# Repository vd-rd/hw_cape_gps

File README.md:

## Overview
Designed for accurate positioning inside embedded projects, this GPS cape offers extended telemetry information, as well as multiple choices for antenna type and placing as well as SoC options.
 The module is designed to accept either:
  - Fibocom GTS-4E-60 (tested)
  - Simcom SIM-28
  - uBlox Neo-M6/7/8
 Regarding connectivity options, the module can be equipped with either an active or passive antenna, connected via a standard u.Fl connector or placed on the carrier PCB.
Detailed information about positioning capabilities of the module can be found in the [GPS](/doc/gps.md) page.

### Project notes
Current development is on the master branch. Earlier revisions have been moved on the archive branch.

### Resources
You can find all necesary information to build or evaluate the module here:
   - [View 3D board render](https://a360.co/2DnqBSM)
   - [Fabrication files](https://github.com/vd-rd/hw_cape_gps/releases)
 
## Features
 - Low power consumption (<30mA)
 - Board can be placed in a true shutdown state (<20uA)
 - Extended temperature range of operation (-40C - 85)
 Detailed information about technical capabilities of the module can be found in the [hardware description](/docs/hardware.md) page.

## Telemetry data
 The module is able to provide standard NMEA sentences on a UART interface. Supported sentences:
 - $GPGGA - Time, position and fix type data
 - $GPGSA - GPS receiver operating mode, satellites used in the position solution, and DOP values
 - $GPGSV - Number of GPS satellites in view satellite ID numbers, elevation, azimuth, & SNR values
 - $GPRMC - Time, date, position, course and speed data
Detailed information about the sentences and parameters can be found in [telemetry](/docs/telemetry.md) page.

## Production
 The module is designed on a 40x40mm double layer PCB, with components placed on a single side for easy assembly.
 The total height of the module (without connectors mounted) is 3mm without the passive antenna mounted and 10mm otherwise.
 Detailed information about the stack-up, BOM and configuration options can be found on the [manufacturing](/docs/manufacturing.md) page.

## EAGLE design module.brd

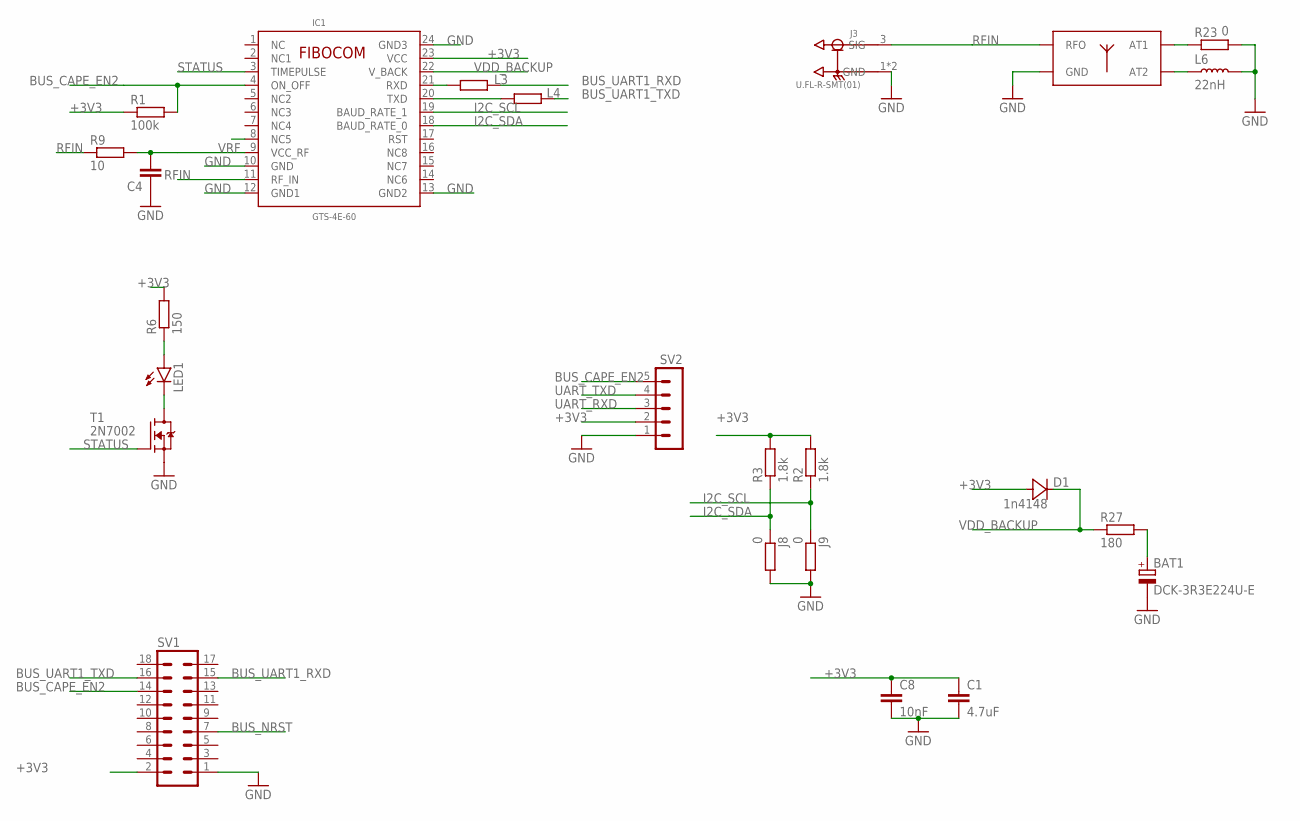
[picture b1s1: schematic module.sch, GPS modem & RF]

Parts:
ANT1: M20047; PCBCOMPONENT_1
BAT1: DCK-3R3E224U-E; 621
C1: 4.7uF; C0603
C4: 10nF; C0402K
C8: 10nF; C0603
D1: 1n4148; SOD323
IC1: GTS-4E-60; _GTS_4E_60
J3: U.FL-R-SMT(01); HRS_U.FL-R-SMT(01)
J8, J9: 0; R0603
L3, L4: blm15; R0603
L6: 22nH; L0402
LED1: LEDCHIP-LED0603; CHIP-LED0603
R1: 100k; R0603
R2, R3: 1.8k; R0603
R6: 150; R0603
R9: 10; R0402
R23: 0; R0402
R27: 180; R0603
SV1: MA09-2
SV2: MA05-1
T1: 2N7002; SOT95P240X110-3

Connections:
+3V3: C1.1, C8.1, D1.A, IC1.23 (VCC), R1.1, R2.2, R3.2, R6.2, SV1.2, SV2.2
BUS_CAPE_EN2: IC1.4 (ON_OFF), R1.2, SV1.14, SV2.5
BUS_NRST: SV1.7
BUS_UART1_RXD: L3.2, SV1.15
BUS_UART1_TXD: L4.2, SV1.16
GND: ANT1.2 (GND), ANT1.3 (GND), ANT1.4 (GND), BAT1.-, C1.2, C4.1, C8.2, IC1.10 (GND), IC1.12 (GND1), IC1.13 (GND2), IC1.24 (GND3), J3.1 (GND), J3.2 (GND), J8.2, J9.2, L6.2, R23.2, SV1.1, SV2.1, T1.2 (S)
I2C_SCL: IC1.19 (BAUD_RATE_1), J9.1, R2.1
I2C_SDA: IC1.18 (BAUD_RATE_0), J8.1, R3.1
unnamed: LED1.C, T1.3 (D)
unnamed: LED1.A, R6.1
unnamed: ANT1.1 (AT1), R23.1
unnamed: ANT1.6 (AT2), L6.1
unnamed: BAT1.+, R27.2
RFIN: ANT1.5 (RFO), IC1.11 (RF_IN), J3.3 (SIG), R9.1
STATUS: IC1.3 (TIMEPULSE), T1.1 (G)
UART_RXD: IC1.20 (TXD), L4.1, SV2.3
UART_TXD: IC1.21 (RXD), L3.1, SV2.4
VDD_BACKUP: D1.K (C), IC1.22 (V_BACK), R27.1
VRF: C4.2, IC1.9 (VCC_RF), R9.2

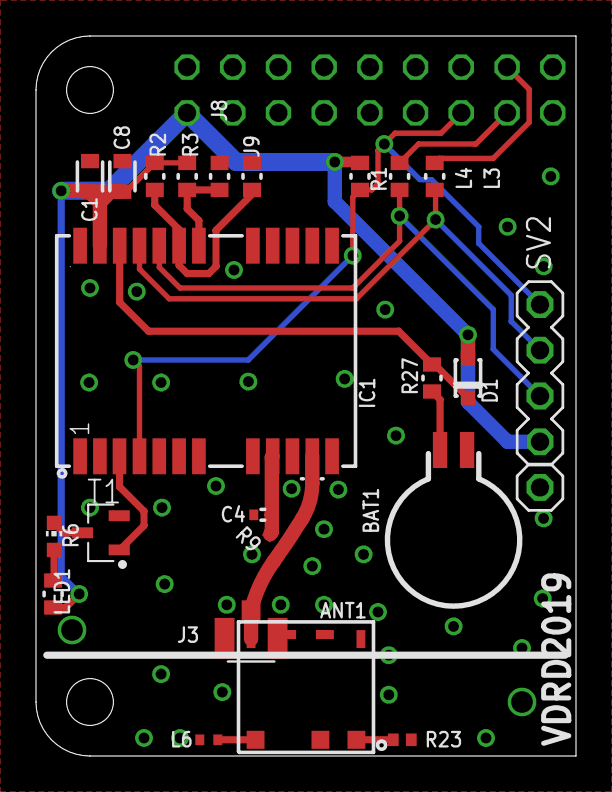
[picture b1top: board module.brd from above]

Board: 2 copper layers, 30.0 x 40.0 mm, 24 parts (1 on the bottom side), 18 nets.

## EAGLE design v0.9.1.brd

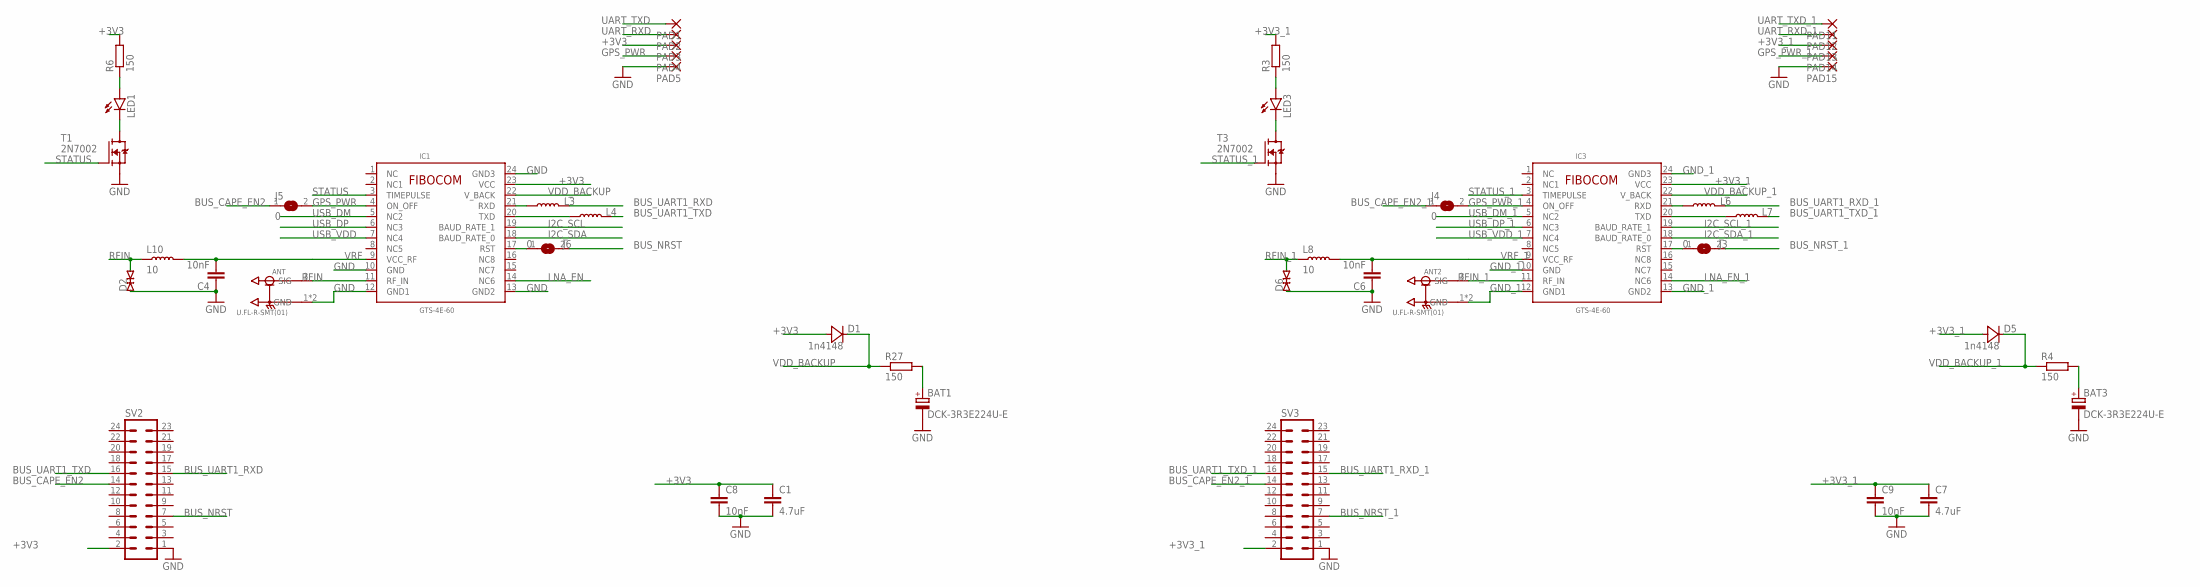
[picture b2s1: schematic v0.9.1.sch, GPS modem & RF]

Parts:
ANT, ANT2: U.FL-R-SMT(01); HRS_U.FL-R-SMT(01)
BAT1, BAT3: DCK-3R3E224U-E; 621
C1, C7: 4.7uF; C0603
C4, C6: 10nF; C0402K
C8, C9: 10nF; C0603
D1, D5: 1n4148; SOD323
D2, D6: ESD9B5.0ST5G; SOD1006X40
IC1, IC3: GTS-4E-60; _GTS_4E_60
J3, J4, J5, J6: 0; C0603
L3, L4, L6, L7: blm15; L0402
L8, L10: 10; L0402
LED1, LED3: LEDCHIP-LED0603; CHIP-LED0603
PAD1, PAD2, PAD3, PAD4, PAD5, PAD11, PAD12, PAD13, PAD14, PAD15: 1,6/0,9
R3, R4, R6, R27: 150; R0603
SV2, SV3: MA12-2
T1, T3: 2N7002; SOT95P240X110-3

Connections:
+3V3: C1.1, C8.1, D1.A, IC1.23 (VCC), PAD3.1, R6.2, SV2.2
+3V3_1: C7.1, C9.1, D5.A, IC3.23 (VCC), PAD13.1, R3.2, SV3.2
BUS_CAPE_EN2: J5.1, SV2.14
BUS_CAPE_EN2_1: J4.1, SV3.14
BUS_NRST: J6.2, SV2.7
BUS_NRST_1: J3.2, SV3.7
BUS_UART1_RXD: L3.2, SV2.15
BUS_UART1_RXD_1: L6.2, SV3.15
BUS_UART1_TXD: L4.2, SV2.16
BUS_UART1_TXD_1: L7.2, SV3.16
GND: ANT.1 (GND), ANT.2 (GND), BAT1.-, C1.2, C4.1, C8.2, D2.1 (A), IC1.10 (GND), IC1.12 (GND1), IC1.13 (GND2), IC1.24 (GND3), PAD5.1, SV2.1, T1.2 (S)
GND_1: ANT2.1 (GND), ANT2.2 (GND), BAT3.-, C6.1, C7.2, C9.2, D6.1 (A), IC3.10 (GND), IC3.12 (GND1), IC3.13 (GND2), IC3.24 (GND3), PAD15.1, SV3.1, T3.2 (S)
GPS_PWR: IC1.4 (ON_OFF), J5.2, PAD4.1
GPS_PWR_1: IC3.4 (ON_OFF), J4.2, PAD14.1
I2C_SCL: IC1.19 (BAUD_RATE_1)
I2C_SCL_1: IC3.19 (BAUD_RATE_1)
I2C_SDA: IC1.18 (BAUD_RATE_0)
I2C_SDA_1: IC3.18 (BAUD_RATE_0)
LNA_EN: IC1.14 (NC6)
LNA_EN_1: IC3.14 (NC6)
unnamed: BAT3.+, R4.2
unnamed: LED1.C, T1.3 (D)
unnamed: IC3.17 (RST), J3.1
unnamed: IC1.17 (RST), J6.1
unnamed: LED3.C, T3.3 (D)
unnamed: LED3.A, R3.1
unnamed: LED1.A, R6.1
unnamed: BAT1.+, R27.2
RFIN: ANT.3 (SIG), D2.2 (C), IC1.11 (RF_IN), L10.1
RFIN_1: ANT2.3 (SIG), D6.2 (C), IC3.11 (RF_IN), L8.1
STATUS: IC1.3 (TIMEPULSE), T1.1 (G)
STATUS_1: IC3.3 (TIMEPULSE), T3.1 (G)
UART_RXD: IC1.20 (TXD), L4.1, PAD2.1
UART_RXD_1: IC3.20 (TXD), L7.1, PAD12.1
UART_TXD: IC1.21 (RXD), L3.1, PAD1.1
UART_TXD_1: IC3.21 (RXD), L6.1, PAD11.1
USB_DM: IC1.5 (NC2)
USB_DM_1: IC3.5 (NC2)
USB_DP: IC1.6 (NC3)
USB_DP_1: IC3.6 (NC3)
USB_VDD: IC1.7 (NC4)
USB_VDD_1: IC3.7 (NC4)
VDD_BACKUP: D1.K (C), IC1.22 (V_BACK), R27.1
VDD_BACKUP_1: D5.K (C), IC3.22 (V_BACK), R4.1
VRF: C4.2, IC1.9 (VCC_RF), L10.2
VRF_1: C6.2, IC3.9 (VCC_RF), L8.2

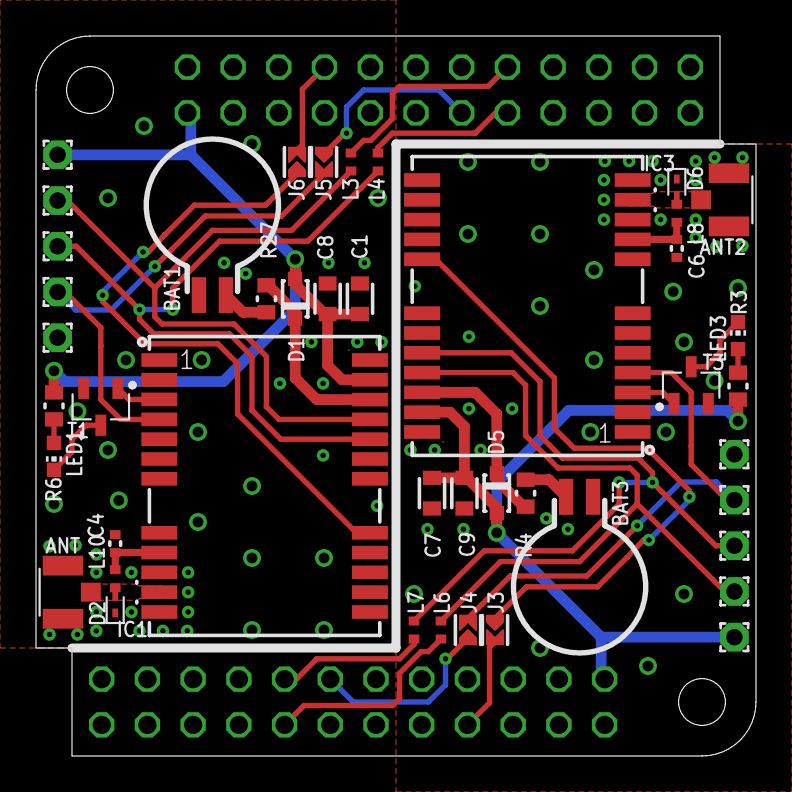
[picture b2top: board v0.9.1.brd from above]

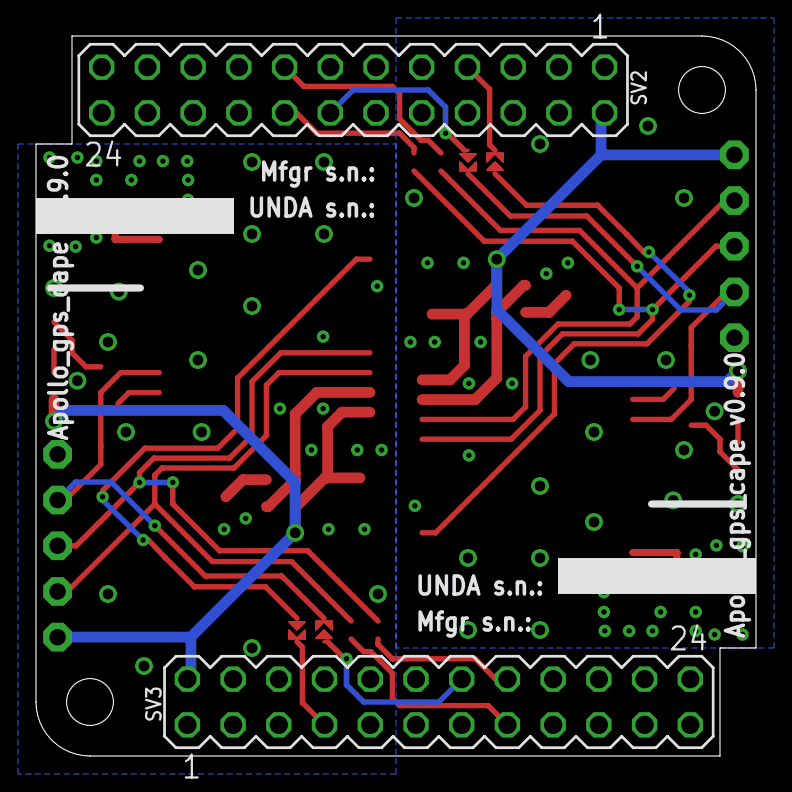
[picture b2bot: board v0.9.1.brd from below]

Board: 2 copper layers, 40.0 x 40.0 mm, 46 parts (2 on the bottom side), 34 nets.

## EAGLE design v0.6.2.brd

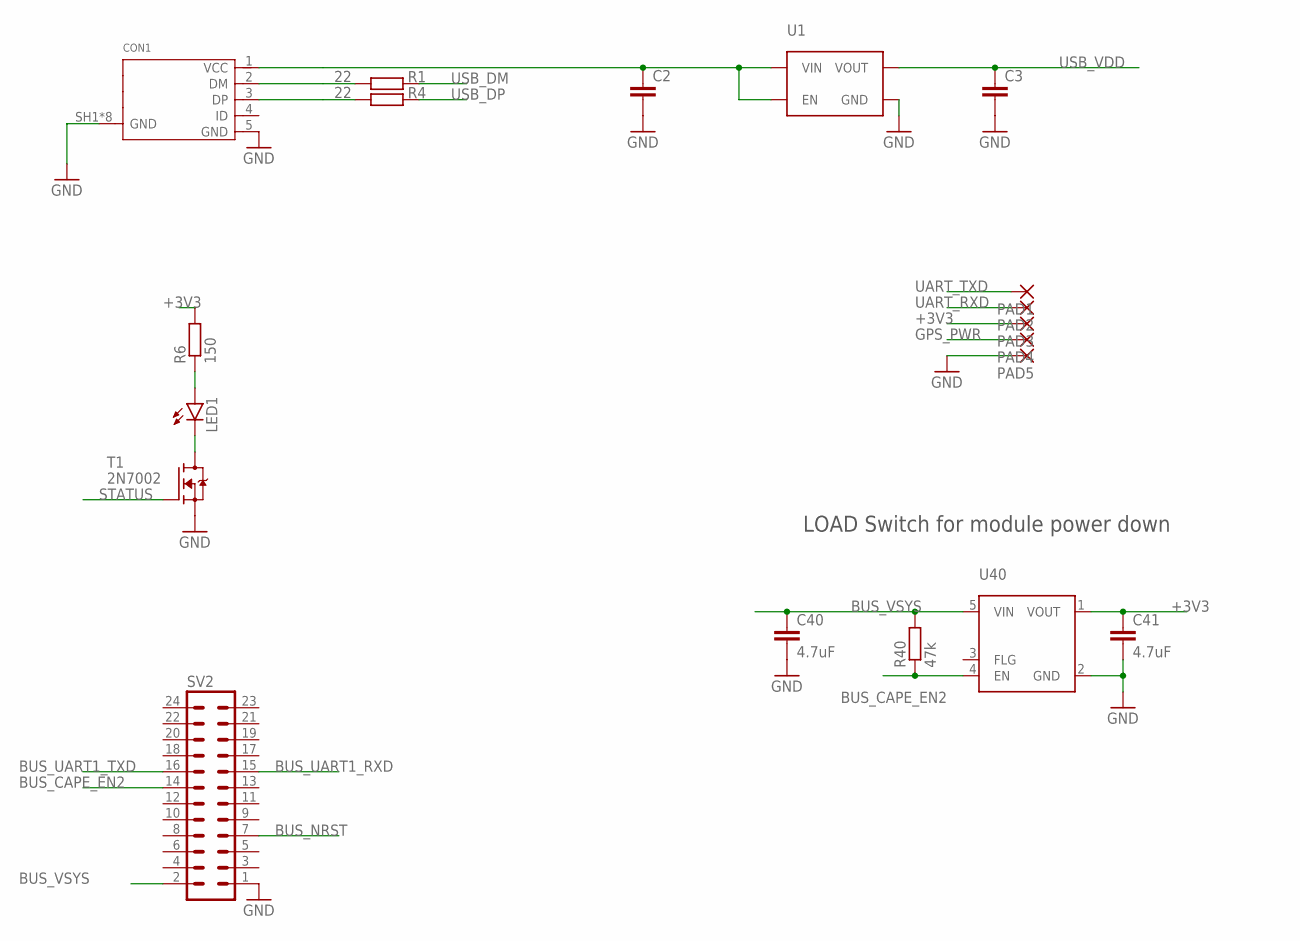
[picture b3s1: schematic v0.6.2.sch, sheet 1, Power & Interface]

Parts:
C2, C3: C-EUC0603; C0603
C40, C41: 4.7uF; C0603
CON1: 10118194-0001LF; 10118194
LED1: LEDCHIP-LED0603; CHIP-LED0603
PAD1, PAD2, PAD3, PAD4, PAD5: 1,6/0,9
R1, R4: 22; R0402
R6: 150; R0402
R40: 47k; R0402
SV2: MA12-2
T1: 2N7002; SOT95P240X110-3
U1: MIC94310; SOT95P280X110-5
U40: AP22802b; SOT25

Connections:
+3V3: C41.1, PAD3.1, R6.2, U40.1 (VOUT); also elsewhere on the board
BUS_CAPE_EN2: R40.1, SV2.14, U40.4 (EN); also elsewhere on the board
BUS_NRST: SV2.7; also elsewhere on the board
BUS_UART1_RXD: SV2.15; also elsewhere on the board
BUS_UART1_TXD: SV2.16; also elsewhere on the board
BUS_VSYS: C40.1, R40.2, SV2.2, U40.5 (VIN)
GND: C2.2, C3.2, C40.2, C41.2, CON1.5 (GND), CON1.SH1 (GND), CON1.SH2 (GND), CON1.SH3 (GND), CON1.SH4 (GND), CON1.SH5 (GND), CON1.SH6 (GND), CON1.SH7 (GND), CON1.SH8 (GND), PAD5.1, SV2.1, T1.2 (S), U1.2 (GND), U40.2 (GND); also elsewhere on the board
GPS_PWR: PAD4.1; also elsewhere on the board
unnamed: LED1.C, T1.3 (D)
unnamed: CON1.2 (DM), R1.2
unnamed: CON1.3 (DP), R4.2
unnamed: LED1.A, R6.1
unnamed: C2.1, CON1.1 (VCC), U1.1 (VIN), U1.3 (EN)
STATUS: T1.1 (G); also elsewhere on the board
UART_RXD: PAD2.1; also elsewhere on the board
UART_TXD: PAD1.1; also elsewhere on the board
USB_DM: R1.1; also elsewhere on the board
USB_DP: R4.1; also elsewhere on the board
USB_VDD: C3.1, U1.5 (VOUT); also elsewhere on the board

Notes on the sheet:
LOAD Switch for module power down

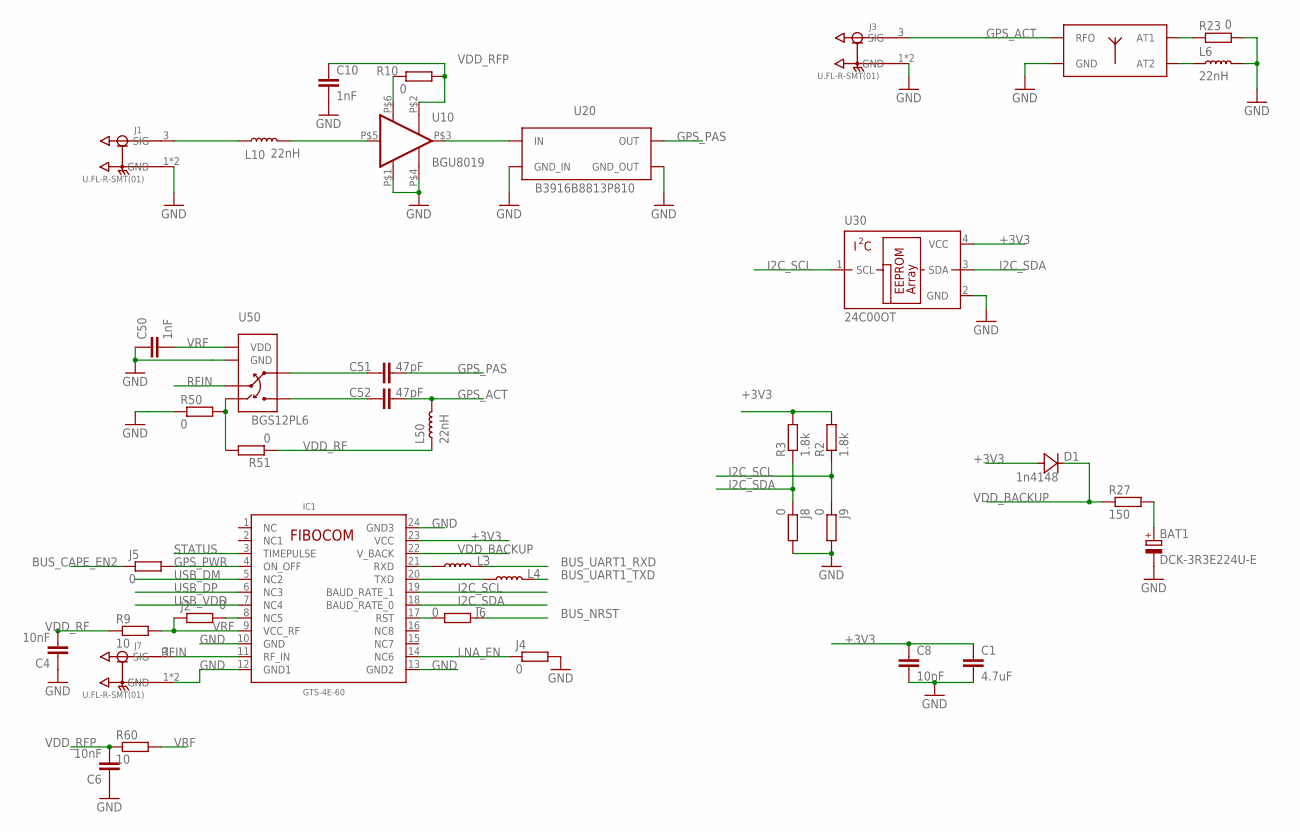
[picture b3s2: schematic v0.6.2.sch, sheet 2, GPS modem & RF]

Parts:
ANT1: M20047; PCBCOMPONENT_1
BAT1: DCK-3R3E224U-E; 621
C1: 4.7uF; C0603
C4, C6, C8: 10nF; C0402K
C10, C50: 1nF; C0402K
C51, C52: 47pF; C0402K
D1: 1n4148; SOD323
IC1: GTS-4E-60; _GTS_4E_60
J1, J3, J7: U.FL-R-SMT(01); HRS_U.FL-R-SMT(01)
J2, J4, J5, J6, J8, J9: 0; R0402
L3, L4: blm15; L0402
L6, L10, L50: 22nH; L0402
R2, R3: 1.8k; R0402
R9, R60: 10; R0402
R10, R23, R50, R51: 0; R0402
R27: 150; R0402
U10: BGU8019; XSON6
U20: B3916B8813P810; XSON5
U30: 24C00OT; SOT23-5L
U50: BGS12PL6; TSLP-6-4

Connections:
+3V3: C1.1, C8.1, D1.A, IC1.23 (VCC), R2.2, R3.2, U30.4 (VCC); also elsewhere on the board
BUS_CAPE_EN2: J5.1; also elsewhere on the board
BUS_NRST: J6.2; also elsewhere on the board
BUS_UART1_RXD: L3.2; also elsewhere on the board
BUS_UART1_TXD: L4.2; also elsewhere on the board
GND: ANT1.2 (GND), ANT1.3 (GND), ANT1.4 (GND), BAT1.-, C1.2, C4.1, C6.1, C8.2, C10.2, C50.1, IC1.10 (GND), IC1.12 (GND1), IC1.13 (GND2), IC1.24 (GND3), J1.1 (GND), J1.2 (GND), J3.1 (GND), J3.2 (GND), J4.2, J7.1 (GND), J7.2 (GND), J8.2, J9.2, L6.2, R23.2, R50.1, U10.P$1 (GND), U10.P$4 (GND_RF), U20.2 (GND_IN), U20.3 (GND_OUT), U20.5 (GND_IN), U30.2 (GND), U50.P$2 (GND); also elsewhere on the board
GPS_ACT: ANT1.5 (RFO), C52.2, J3.3 (SIG), L50.2
GPS_PAS: C51.2, U20.4 (OUT)
GPS_PWR: IC1.4 (ON_OFF), J5.2; also elsewhere on the board
I2C_SCL: IC1.19 (BAUD_RATE_1), J9.1, R2.1, U30.1 (SCL)
I2C_SDA: IC1.18 (BAUD_RATE_0), J8.1, R3.1, U30.3 (SDA)
LNA_EN: IC1.14 (NC6), J4.1
unnamed: IC1.8 (NC5), J2.2
unnamed: U10.P$3 (RF_OUT), U20.1 (IN)
unnamed: R10.1, U10.P$6 (ENABLE)
unnamed: L10.2, U10.P$5 (RF_IN)
unnamed: J1.3 (SIG), L10.1
unnamed: IC1.17 (RST), J6.1
unnamed: R50.2, R51.2, U50.P$6
unnamed: C51.1, U50.P$3 (RF1)
unnamed: C52.1, U50.P$1 (RF2)
unnamed: ANT1.1 (AT1), R23.1
unnamed: ANT1.6 (AT2), L6.1
unnamed: BAT1.+, R27.2
RFIN: IC1.11 (RF_IN), J7.3 (SIG), U50.P$5 (RFIN)
STATUS: IC1.3 (TIMEPULSE); also elsewhere on the board
UART_RXD: IC1.20 (TXD), L4.1; also elsewhere on the board
UART_TXD: IC1.21 (RXD), L3.1; also elsewhere on the board
USB_DM: IC1.5 (NC2); also elsewhere on the board
USB_DP: IC1.6 (NC3); also elsewhere on the board
USB_VDD: IC1.7 (NC4); also elsewhere on the board
VDD_BACKUP: D1.K (C), IC1.22 (V_BACK), R27.1
VDD_RF: C4.2, L50.1, R9.1, R51.1
VDD_RFP: C6.2, C10.1, R10.2, R60.1, U10.P$2 (VCC)
VRF: C50.2, IC1.9 (VCC_RF), J2.1, R9.2, R60.2, U50.P$4 (VDD)

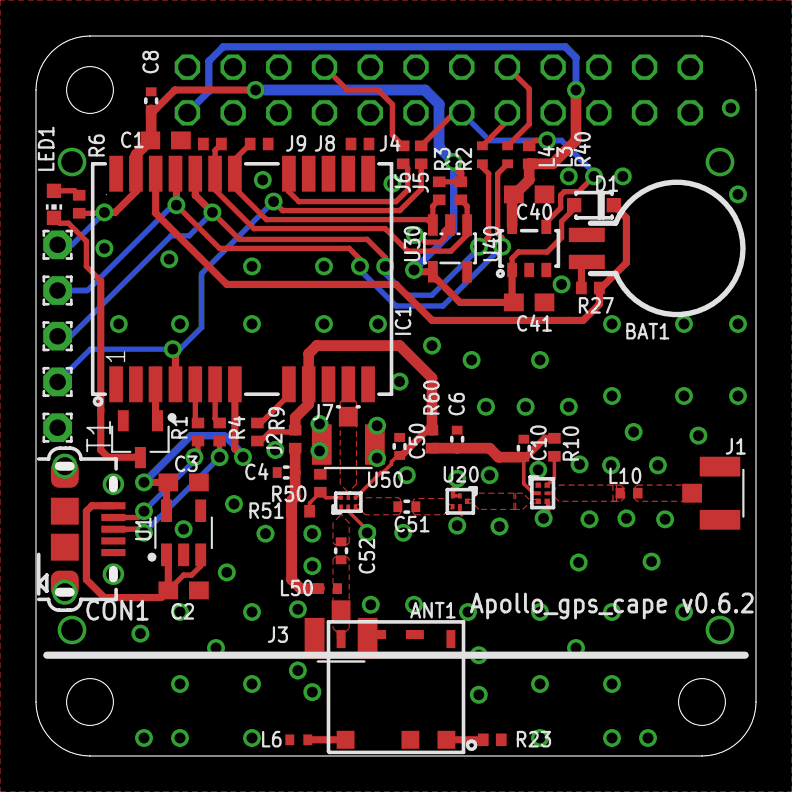
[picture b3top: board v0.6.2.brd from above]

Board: 2 copper layers, 40.0 x 40.0 mm, 58 parts (1 on the bottom side), 41 nets.

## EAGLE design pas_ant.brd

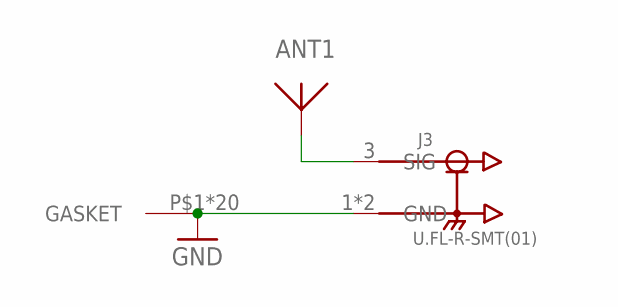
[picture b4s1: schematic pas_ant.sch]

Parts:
ANT1: ANT1590-2540A; 2540A
J3: U.FL-R-SMT(01); HRS_U.FL-R-SMT(01)
U$1: 2118718-2; 2118717-2

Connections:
GND2: J3.1 (GND), J3.2 (GND), U$1.P$1, U$1.P$2, U$1.P$3, U$1.P$4, U$1.P$5, U$1.P$6, U$1.P$7, U$1.P$8, U$1.P$9, U$1.P$10, U$1.P$11, U$1.P$12, U$1.P$13, U$1.P$14, U$1.P$15, U$1.P$16, U$1.P$17, U$1.P$18, U$1.P$19, U$1.P$20
unnamed: ANT1.P$1, J3.3 (SIG)

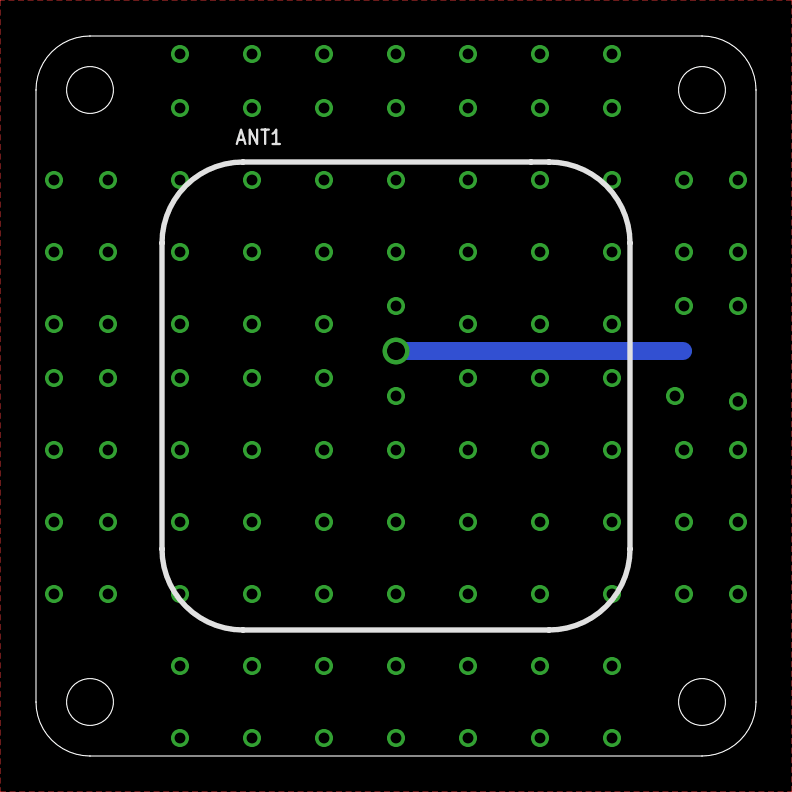
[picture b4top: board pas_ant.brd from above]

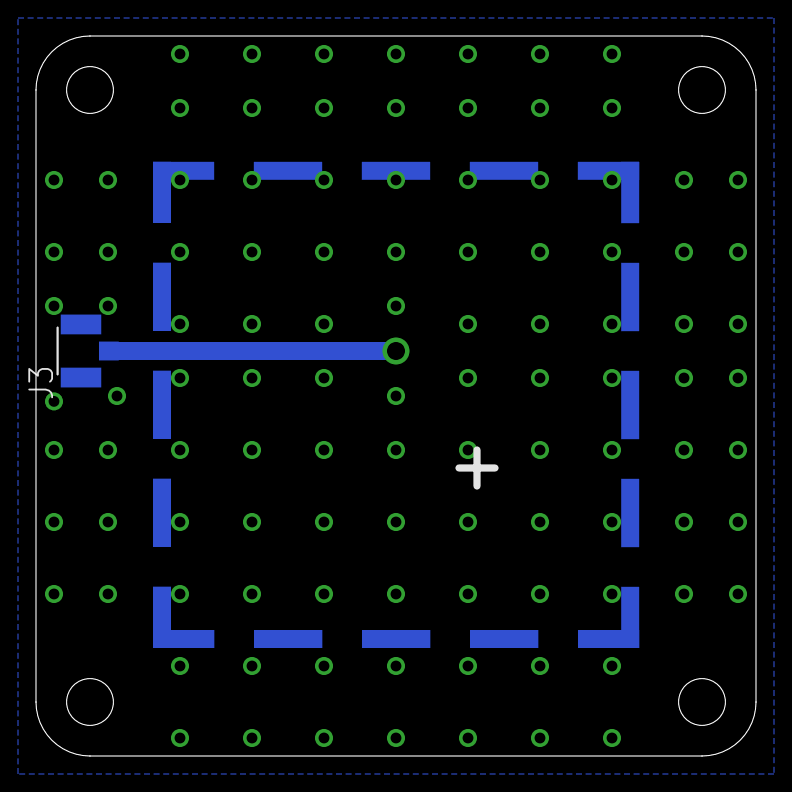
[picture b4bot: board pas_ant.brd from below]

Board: 2 copper layers, 40.0 x 40.0 mm, 3 parts (2 on the bottom side), 2 nets.

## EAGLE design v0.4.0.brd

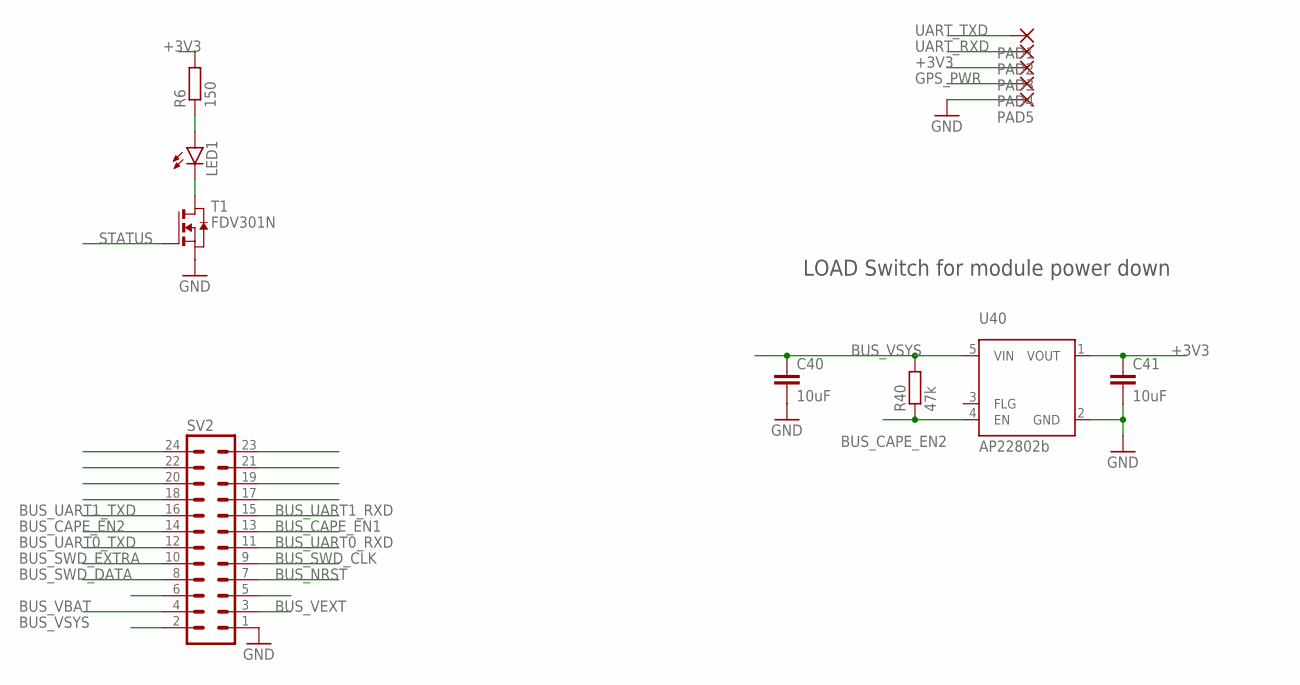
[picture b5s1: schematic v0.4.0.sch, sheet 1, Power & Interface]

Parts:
C40, C41: 10uF; C0603
LED1: LEDCHIP-LED0603; CHIP-LED0603
PAD1, PAD2, PAD3, PAD4, PAD5: 1,6/0,9
R6: 150; R0402
R40: 47k; R0402
SV2: MA12-2
T1: FDV301N; SOT-23
U40: AP22802b; SOT25

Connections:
+3V3: C41.1, PAD3.1, R6.2, U40.1 (VOUT); also elsewhere on the board
BUS_CAPE_EN1: SV2.13
BUS_CAPE_EN2: R40.1, SV2.14, U40.4 (EN); also elsewhere on the board
BUS_NRST: SV2.7; also elsewhere on the board
BUS_SWD_CLK: SV2.9
BUS_SWD_DATA: SV2.8
BUS_SWD_EXTRA: SV2.10
BUS_UART0_RXD: SV2.11
BUS_UART0_TXD: SV2.12
BUS_UART1_RXD: SV2.15; also elsewhere on the board
BUS_UART1_TXD: SV2.16; also elsewhere on the board
BUS_VBAT: SV2.4
BUS_VEXT: SV2.3
BUS_VSYS: C40.1, R40.2, SV2.2, U40.5 (VIN)
GND: C40.2, C41.2, PAD5.1, SV2.1, T1.2 (S), U40.2 (GND); also elsewhere on the board
GPS_PWR: PAD4.1; also elsewhere on the board
unnamed: LED1.C, T1.1 (D)
unnamed: LED1.A, R6.1
STATUS: T1.3 (G); also elsewhere on the board
UART_RXD: PAD2.1; also elsewhere on the board
UART_TXD: PAD1.1; also elsewhere on the board

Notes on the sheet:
LOAD Switch for module power down

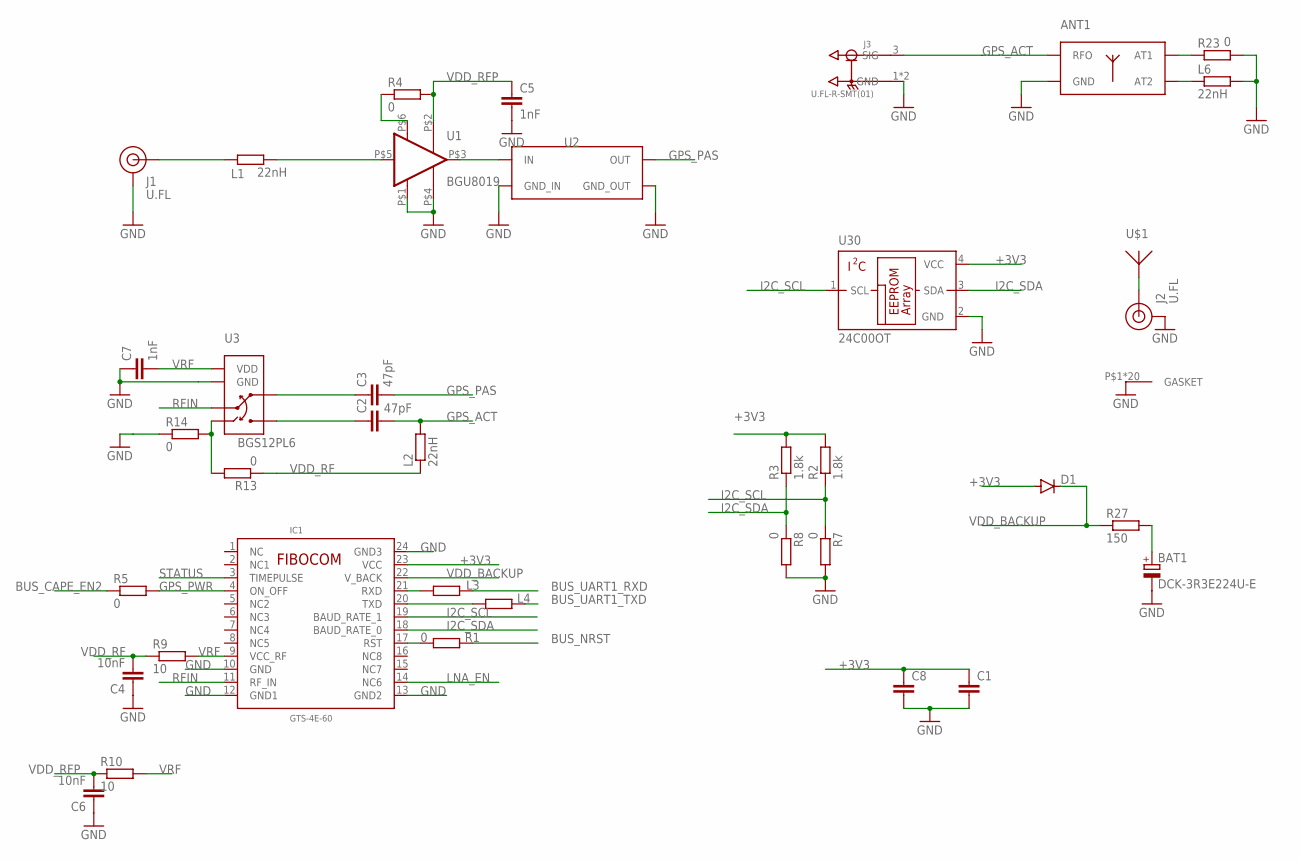
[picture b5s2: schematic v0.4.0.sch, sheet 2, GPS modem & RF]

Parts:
ANT1: M20047; PCBCOMPONENT_1
BAT1: DCK-3R3E224U-E; 621
C1: C-EUC0603; C0603
C2, C3: 47pF; C0402
C4, C6: 10nF; C0402
C5, C7: 1nF; C0402
C8: C-EUC0402; C0402
D1: DIODE-SOD323-R; SOD323-R
IC1: GTS-4E-60; _GTS_4E_60
J1, J2: U.FL
J3: U.FL-R-SMT(01); HRS_U.FL-R-SMT(01)
L1, L2, L6: 22nH; R0402
L3, L4: R-EU_R0402; R0402
R1, R4, R5, R7, R8, R13, R14, R23: 0; R0402
R2, R3: 1.8k; R0402
R9, R10: 10; R0402
R27: 150; R0402
U1: BGU8019; XSON6
U2: B3916B8813P810; XSON5
U3: BGS12PL6; TSLP-6-4
U30: 24C00OT; SOT23-5L
U$1: ANT1590-2540A; 2540A
U$2: 2118718-2; 2118717-2

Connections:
+3V3: C1.1, C8.1, D1.A, IC1.23 (VCC), R2.2, R3.2, U30.4 (VCC); also elsewhere on the board
BUS_CAPE_EN2: R5.1; also elsewhere on the board
BUS_NRST: R1.2; also elsewhere on the board
BUS_UART1_RXD: L3.2; also elsewhere on the board
BUS_UART1_TXD: L4.2; also elsewhere on the board
GND: ANT1.2 (GND), ANT1.3 (GND), ANT1.4 (GND), BAT1.-, C1.2, C4.1, C5.2, C6.1, C7.1, C8.2, IC1.10 (GND), IC1.12 (GND1), IC1.13 (GND2), IC1.24 (GND3), J1.1 (GND), J1.2 (GND), J2.1 (GND), J2.2 (GND), J3.1 (GND), J3.2 (GND), L6.2, R7.2, R8.2, R14.1, R23.2, U1.P$1 (GND), U1.P$4 (GND_RF), U2.2 (GND_IN), U2.3 (GND_OUT), U2.5 (GND_IN), U3.P$2 (GND), U30.2 (GND), U$2.P$1, U$2.P$2, U$2.P$3, U$2.P$4, U$2.P$5, U$2.P$6, U$2.P$7, U$2.P$8, U$2.P$9, U$2.P$10, U$2.P$11, U$2.P$12, U$2.P$13, U$2.P$14, U$2.P$15, U$2.P$16, U$2.P$17, U$2.P$18, U$2.P$19, U$2.P$20; also elsewhere on the board
GPS_ACT: ANT1.5 (RFO), C2.2, J3.3 (SIG), L2.2
GPS_PAS: C3.2, U2.4 (OUT)
GPS_PWR: IC1.4 (ON_OFF), R5.2; also elsewhere on the board
I2C_SCL: IC1.19 (BAUD_RATE_1), R2.1, R7.1, U30.1 (SCL)
I2C_SDA: IC1.18 (BAUD_RATE_0), R3.1, R8.1, U30.3 (SDA)
LNA_EN: IC1.14 (NC6)
unnamed: J2.FEED (SIGNAL), U$1.P$1
unnamed: U1.P$3 (RF_OUT), U2.1 (IN)
unnamed: R4.1, U1.P$6 (ENABLE)
unnamed: L1.2, U1.P$5 (RF_IN)
unnamed: J1.FEED (SIGNAL), L1.1
unnamed: IC1.17 (RST), R1.1
unnamed: R13.2, R14.2, U3.P$6
unnamed: C3.1, U3.P$3 (RF1)
unnamed: C2.1, U3.P$1 (RF2)
unnamed: ANT1.1 (AT1), R23.1
unnamed: ANT1.6 (AT2), L6.1
unnamed: BAT1.+, R27.2
RFIN: IC1.11 (RF_IN), U3.P$5 (RFIN)
STATUS: IC1.3 (TIMEPULSE); also elsewhere on the board
UART_RXD: IC1.20 (TXD), L4.1; also elsewhere on the board
UART_TXD: IC1.21 (RXD), L3.1; also elsewhere on the board
VDD_BACKUP: D1.C, IC1.22 (V_BACK), R27.1
VDD_RF: C4.2, L2.1, R9.1, R13.1
VDD_RFP: C5.1, C6.2, R4.2, R10.1, U1.P$2 (VCC)
VRF: C7.2, IC1.9 (VCC_RF), R9.2, R10.2, U3.P$4 (VDD)

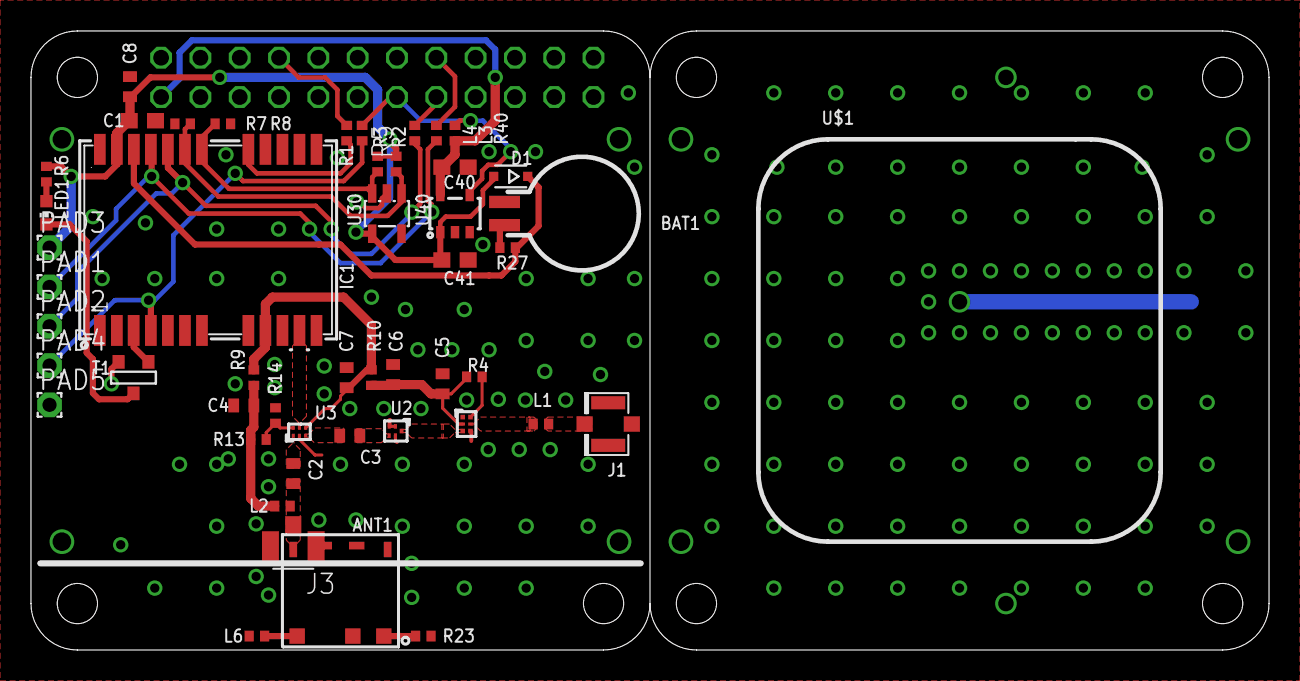
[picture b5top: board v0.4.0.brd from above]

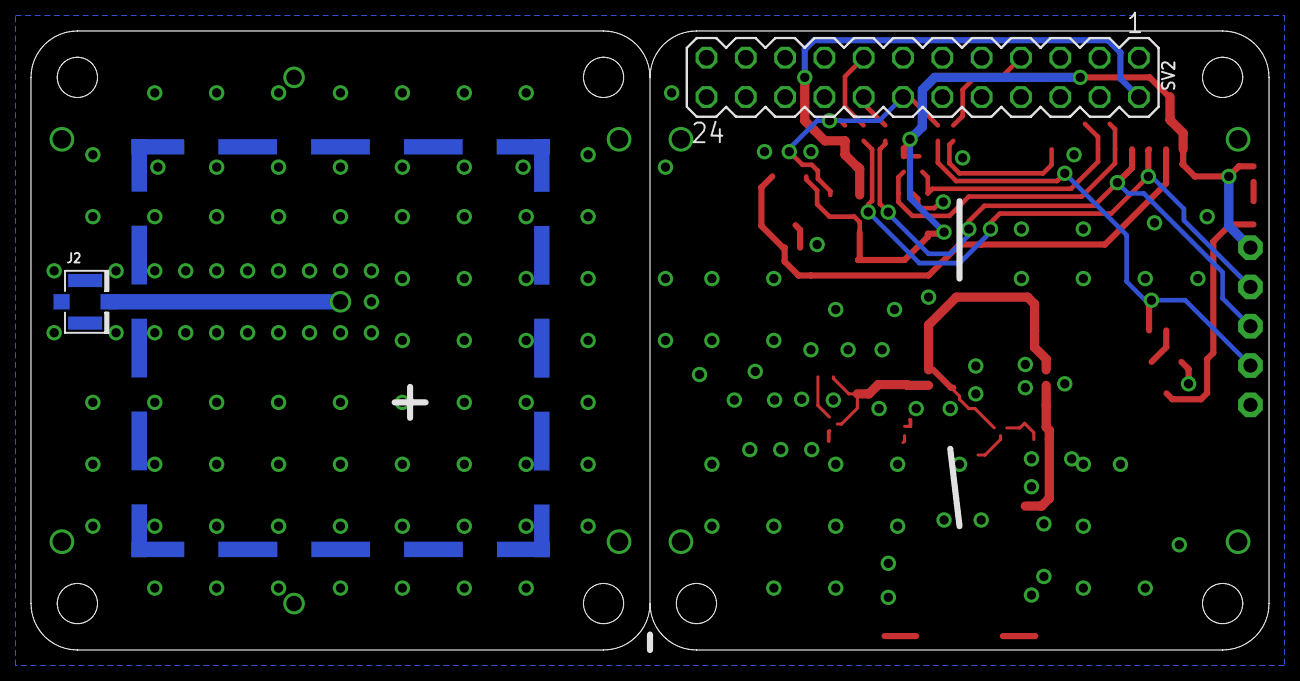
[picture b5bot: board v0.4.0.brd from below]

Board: 2 copper layers, 80.0 x 40.0 mm, 52 parts (3 on the bottom side), 34 nets.

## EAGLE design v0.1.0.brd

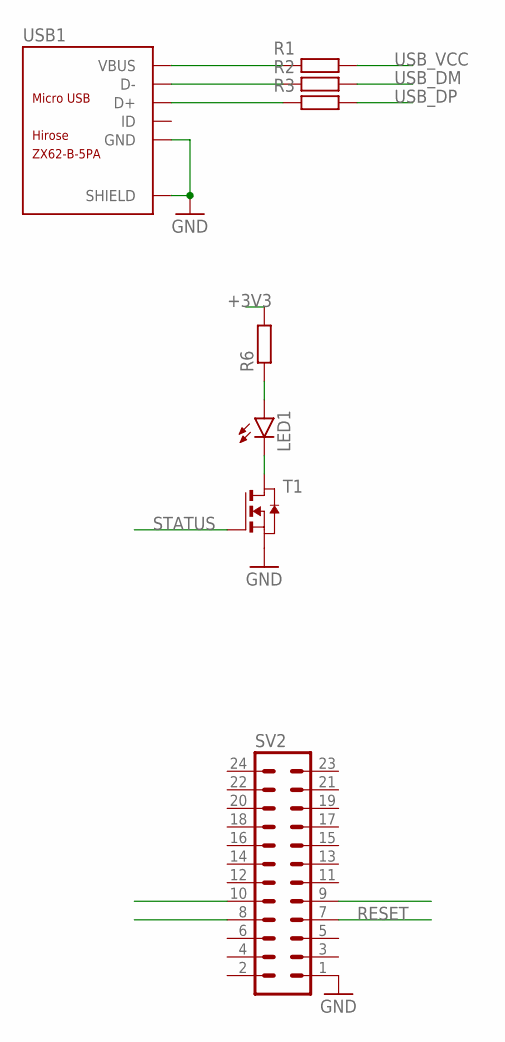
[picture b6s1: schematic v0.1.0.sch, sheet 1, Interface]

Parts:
LED1: LEDCHIP-LED0603; CHIP-LED0603
R1, R2, R3, R6: R-EU_R0402; R0402
SV2: MA12-2
T1: NMOSSOT23; SOT-23
USB1: ZX62-B-5PA; MICRO-USB5+6P-SMD-0.65-AB

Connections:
+3V3: R6.2; also elsewhere on the board
GND: SV2.1, T1.2 (S), USB1.5 (GND), USB1.P1 (SHIELD), USB1.P2 (SHIELD), USB1.P3 (SHIELD), USB1.P4 (SHIELD), USB1.P5 (SHIELD), USB1.P6 (SHIELD); also elsewhere on the board
unnamed: LED1.C, T1.1 (D)
unnamed: R2.1, USB1.2 (D-)
unnamed: R3.1, USB1.3 (D+)
unnamed: LED1.A, R6.1
RESET: SV2.7; also elsewhere on the board
STATUS: T1.3 (G); also elsewhere on the board
USB_DM: R2.2; also elsewhere on the board
USB_DP: R3.2; also elsewhere on the board
USB_VCC: R1.2; also elsewhere on the board
VBUS: R1.1, USB1.1 (VBUS)

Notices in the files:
parts and their libraries:
SparkFun-Connectors: Licensing: Creative Commons ShareAlike 4.0 International - https://creativecommons.org/licenses/by-sa/4.0
